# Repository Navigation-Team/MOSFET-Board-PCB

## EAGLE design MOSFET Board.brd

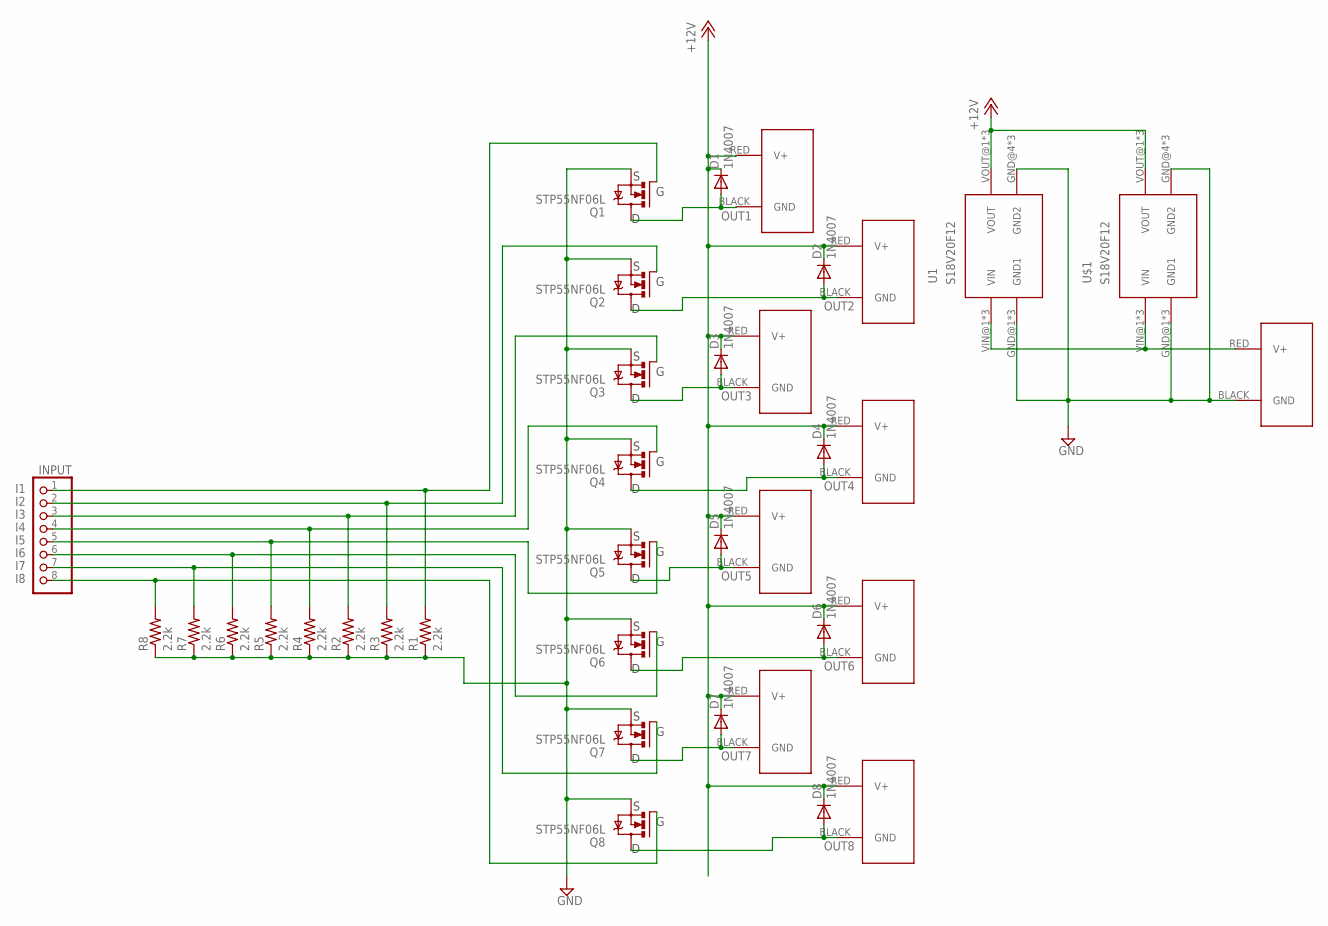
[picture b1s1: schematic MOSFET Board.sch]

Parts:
D1, D2, D3, D4, D5, D6, D7, D8: 1N4007; DO41-10
INPUT: PINHD-1X8; 1X08
J1, J2, J3, J4, J5, J6, J7, J8, J9: POWERPOLE_POWER25A; POWERPOLE_PAIR_25A
Q1, Q2, Q3, Q4, Q5, Q6, Q7, Q8: STP55NF06L; TO220-3
R1, R2, R3, R4, R5, R6, R7, R8: 2.2k; 0207/10
U1: S18V20F12; S18V20
U$1: S18V20F12; S18V20

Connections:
+12V: D1.C, D2.C, D3.C, D4.C, D5.C, D6.C, D7.C, D8.C, J2.RED (V+), J3.RED (V+), J4.RED (V+), J5.RED (V+), J6.RED (V+), J7.RED (V+), J8.RED (V+), J9.RED (V+), U1.VOUT@1 (VOUT), U1.VOUT@2 (VOUT), U1.VOUT@3 (VOUT), U$1.VOUT@1 (VOUT), U$1.VOUT@2 (VOUT), U$1.VOUT@3 (VOUT)
GND: J1.BLACK (GND), Q1.S, Q2.S, Q3.S, Q4.S, Q5.S, Q6.S, Q7.S, Q8.S, R1.1, R2.1, R3.1, R4.1, R5.1, R6.1, R7.1, R8.1, U1.GND@1 (GND1), U1.GND@2 (GND1), U1.GND@3 (GND1), U1.GND@4 (GND2), U1.GND@5 (GND2), U1.GND@6 (GND2), U$1.GND@1 (GND1), U$1.GND@2 (GND1), U$1.GND@3 (GND1), U$1.GND@4 (GND2), U$1.GND@5 (GND2), U$1.GND@6 (GND2)
I1: INPUT.1, Q1.G, R1.2
I2: INPUT.2, Q2.G, R3.2
I3: INPUT.3, Q3.G, R2.2
I4: INPUT.4, Q4.G, R4.2
I5: INPUT.5, Q5.G, R5.2
I6: INPUT.6, Q6.G, R6.2
I7: INPUT.7, Q7.G, R7.2
I8: INPUT.8, Q8.G, R8.2
OUT1: D1.A, J2.BLACK (GND), Q1.D
OUT2: D2.A, J3.BLACK (GND), Q2.D
OUT3: D3.A, J4.BLACK (GND), Q3.D
OUT4: D4.A, J5.BLACK (GND), Q4.D
OUT5: D5.A, J6.BLACK (GND), Q5.D
OUT6: D6.A, J7.BLACK (GND), Q6.D
OUT7: D7.A, J8.BLACK (GND), Q7.D
OUT8: D8.A, J9.BLACK (GND), Q8.D
VIN: J1.RED (V+), U1.VIN@1 (VIN), U1.VIN@2 (VIN), U1.VIN@3 (VIN), U$1.VIN@1 (VIN), U$1.VIN@2 (VIN), U$1.VIN@3 (VIN)

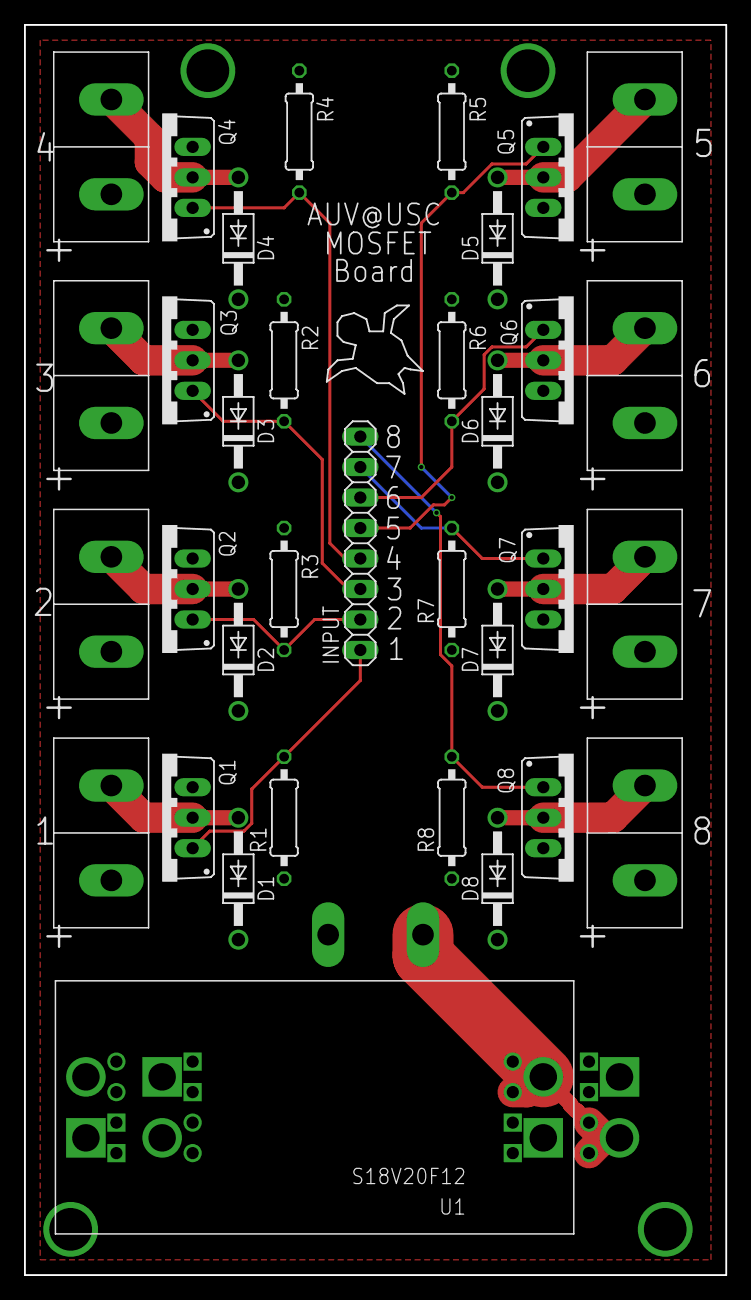
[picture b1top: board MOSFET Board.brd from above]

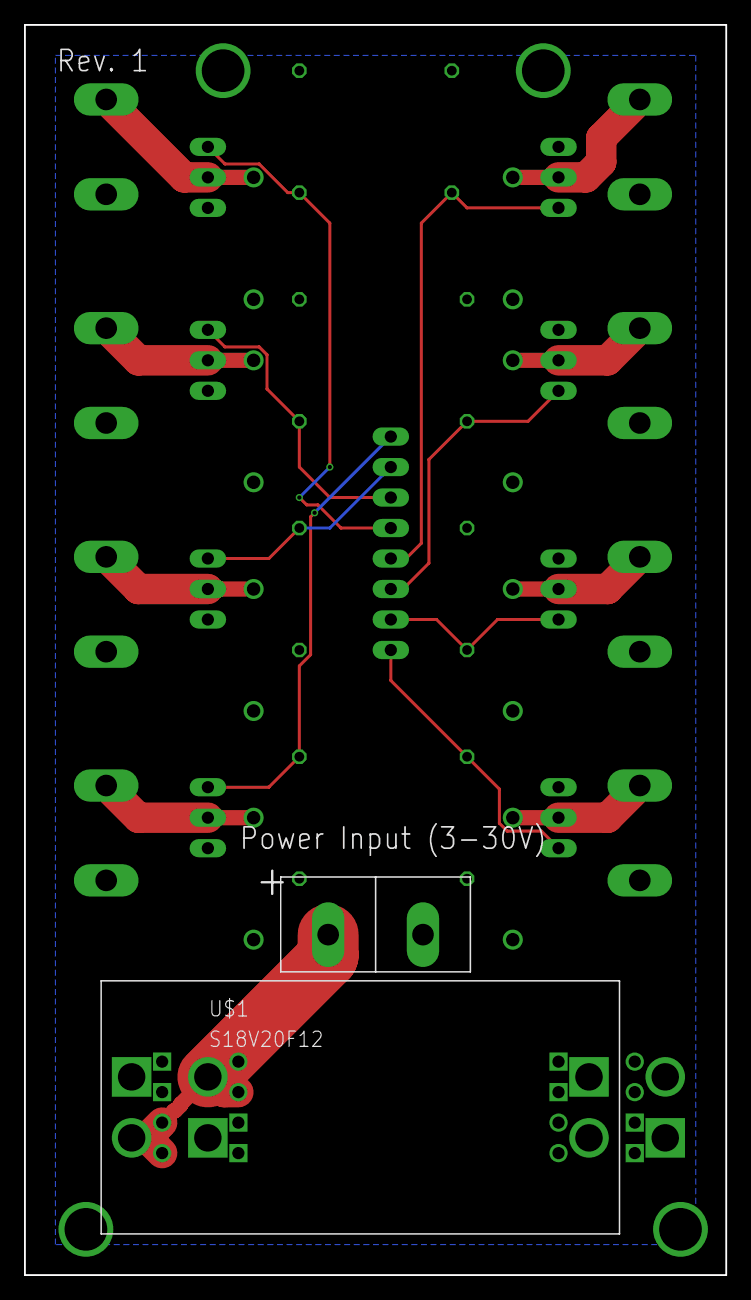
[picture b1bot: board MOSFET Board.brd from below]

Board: 2 copper layers, 58.4 x 104.1 mm, 36 parts (2 on the bottom side), 19 nets.

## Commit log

2018-05-01 Initial commit, done with initial design of board
2018-05-01 Add version marker
2018-06-25 Add numbers to outputs on silkscreen
